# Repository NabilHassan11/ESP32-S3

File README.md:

# ESP32-S3-Mini-1-N8 Development Board

## Overview

This is a custom ESP32-S3-Mini-1-N8 development board designed for embedded systems and IoT applications. It provides an easy-to-use platform for programming, debugging, and prototyping ESP32-based projects.

## Features

✅ **RGB LED & Temperature Sensor**: Onboard RGB LED and temperature sensor for enhanced functionality

✅ **Microcontroller: ESP32-S3-Mini-1-N8 (Wi-Fi and Bluetooth LE support)**

✅ **Power Input: 3.3V regulated supply**
✅ **Reset & Boot Buttons:** Tactile push buttons for RESET and BOOT mode selection
✅ **Connectivity:** I2C header for external sensors and peripherals
    Multiple GPIO breakout pins for external components
✅ **Power Regulation:** Onboard LDO voltage regulator for stable 3.3V operation

## Applications

-IoT prototyping

-Wireless sensor networks

-Home automation

-Embedded systems development

Repository Contents

## Repository Contents
📁 **Hardware:** KiCad design files, schematics, and PCB layout
📁 **Documentation:** BOM, assembly guide, and pinout diagrams 

---
### Author
**Nabil Hassan**

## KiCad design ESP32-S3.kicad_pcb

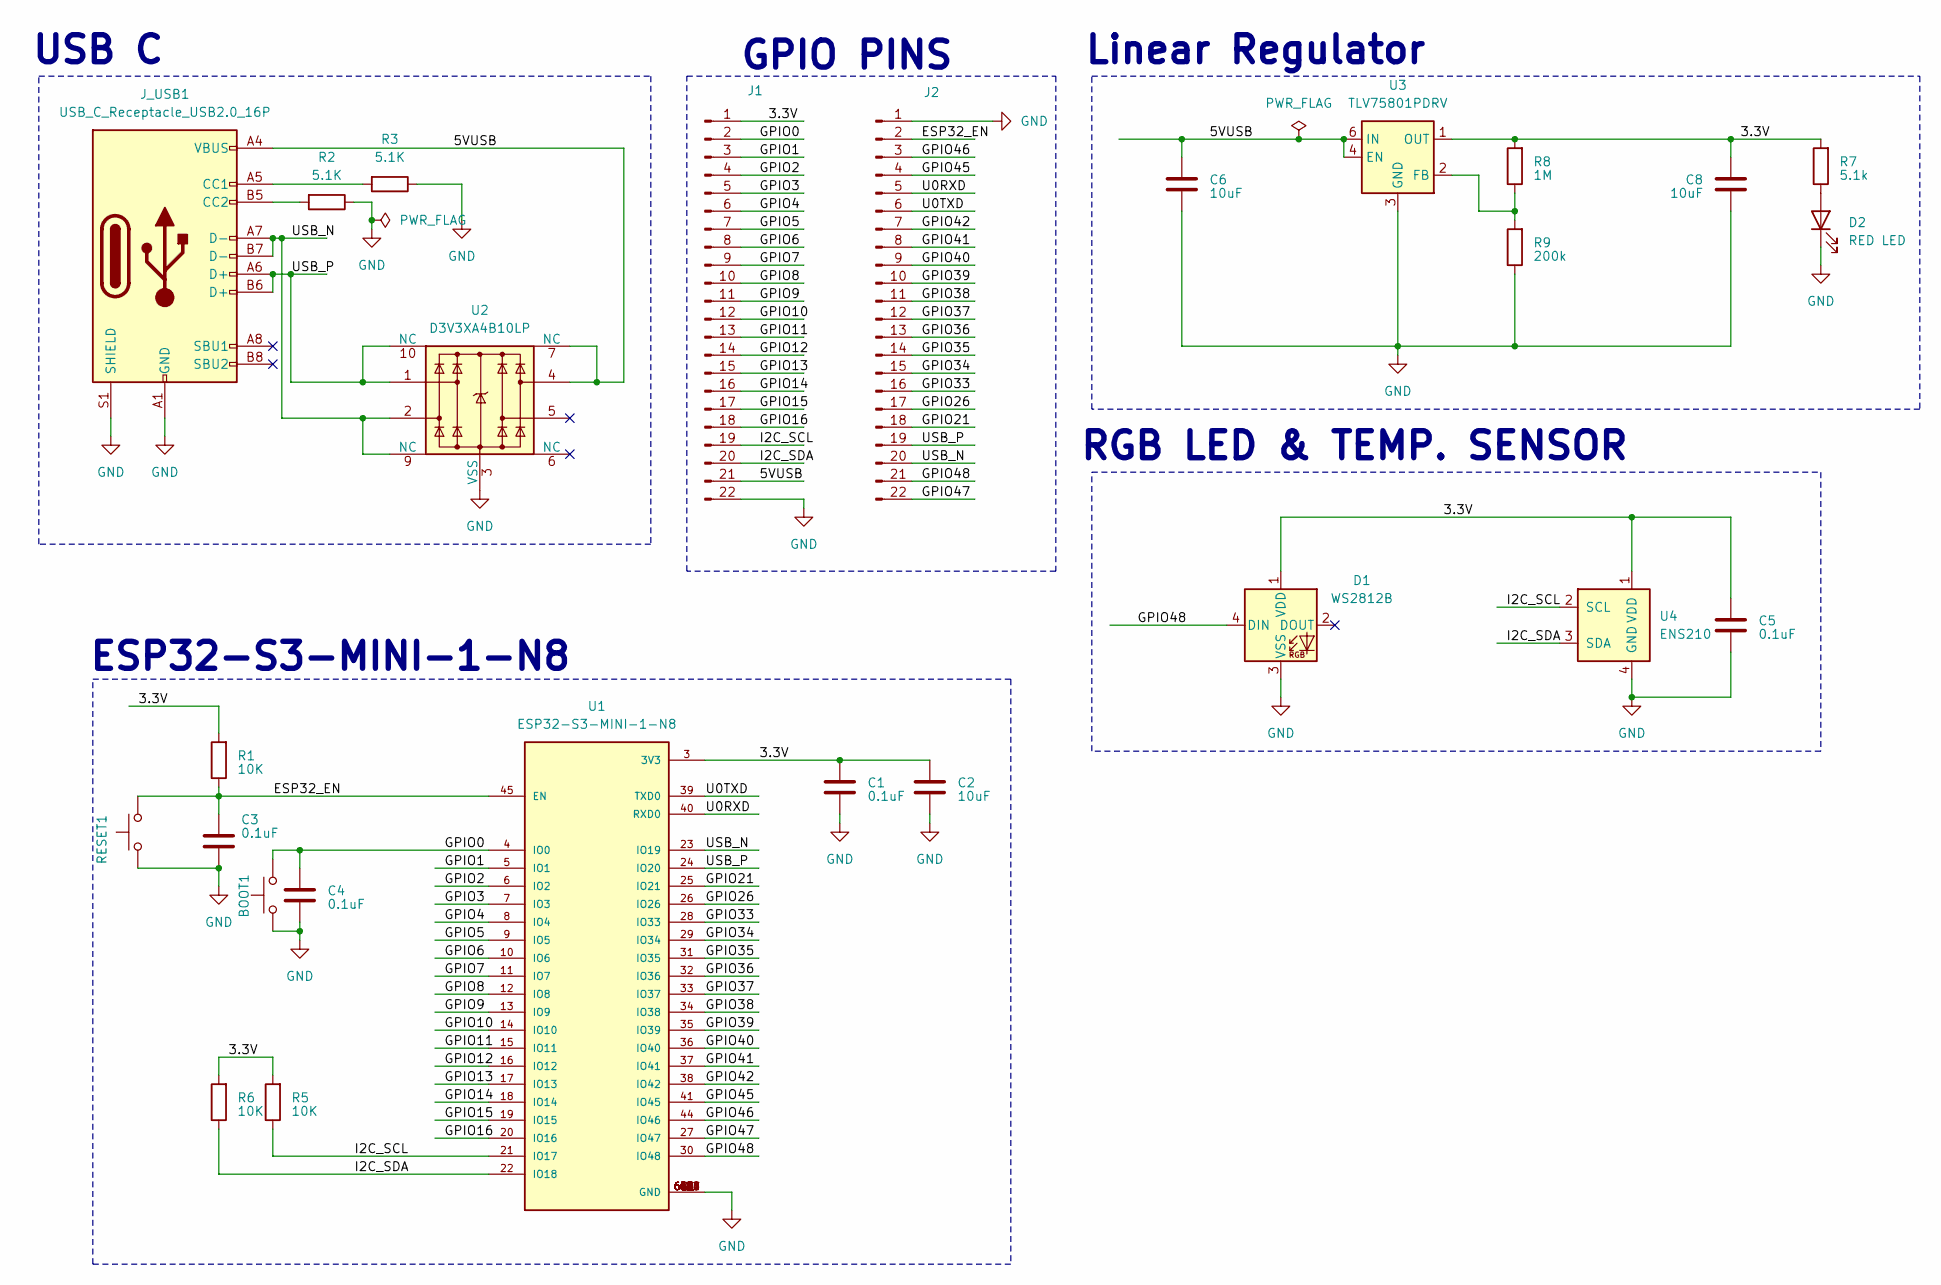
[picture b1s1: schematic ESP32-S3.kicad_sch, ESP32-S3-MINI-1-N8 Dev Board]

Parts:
BOOT1: SW_SPST_PTS810
C1, C3, C4, C5: 0.1uF; C_0201_0603Metric
C2, C6, C8: 10uF; C_0603_1608Metric
D1: WS2812B; LED_WS2812B_PLCC4_5.0x5.0mm_P3.2mm
D2: RED LED; LED_0201_0603Metric
J1, J2: Conn_01x22_Pin; PinHeader_1x22_P2.54mm_Vertical
J_USB1: USB_C_Receptacle_USB2.0_16P; USB_C_Receptacle_GCT_USB4105-xx-A_16P_TopMnt_Horizontal
R1, R5, R6: 10K; R_0201_0603Metric
R2, R3: 5.1K; R_0201_0603Metric
R7: 5.1k; R_0201_0603Metric
R8: 1M; R_0201_0603Metric
R9: 200k; R_0201_0603Metric
RESET1: SW_Push; SW_SPST_PTS810
U1: ESP32-S3-MINI-1-N8; XCVR_ESP32-S3-MINI-1-N8; PARTREV v0.6; DigiKey_Part_Number 1965-ESP32-S3-MINI-1-N8TR-ND
U2: D3V3XA4B10LP; Diodes_UDFN-10_1.0x2.5mm_P0.5mm
U3: TLV75801PDRV; WSON-6-1EP_2x2mm_P0.65mm_EP1x1.6mm
U4: ENS210; AMS_QFN-4-1EP_2x2mm_P0.95mm_EP0.7x1.6mm

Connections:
/3.3V: C1.1, C2.1, C5.1, C8.1, D1.1 (VDD), J1.1, R1.2, R5.2, R6.2, R7.2, R8.2, U1.3 (3V3), U3.1 (OUT), U4.1 (VDD)
/5VUSB: C6.1, J1.21, J_USB1.A4 (VBUS), J_USB1.A9 (VBUS), J_USB1.B4 (VBUS), J_USB1.B9 (VBUS), U2.4, U2.7 (NC), U3.4 (EN), U3.6 (IN)
/ESP32_EN: C3.1, J2.2, R1.1, RESET1.2, U1.45 (EN)
/GPIO0: BOOT1.2, C4.1, J1.2, U1.4 (IO0)
/GPIO1: J1.3, U1.5 (IO1)
/GPIO2: J1.4, U1.6 (IO2)
/GPIO3: J1.5, U1.7 (IO3)
/GPIO4: J1.6, U1.8 (IO4)
/GPIO5: J1.7, U1.9 (IO5)
/GPIO6: J1.8, U1.10 (IO6)
/GPIO7: J1.9, U1.11 (IO7)
/GPIO8: J1.10, U1.12 (IO8)
/GPIO9: J1.11, U1.13 (IO9)
/GPIO10: J1.12, U1.14 (IO10)
/GPIO11: J1.13, U1.15 (IO11)
/GPIO12: J1.14, U1.16 (IO12)
/GPIO13: J1.15, U1.17 (IO13)
/GPIO14: J1.16, U1.18 (IO14)
/GPIO15: J1.17, U1.19 (IO15)
/GPIO16: J1.18, U1.20 (IO16)
/GPIO21: J2.18, U1.25 (IO21)
/GPIO26: J2.17, U1.26 (IO26)
/GPIO33: J2.16, U1.28 (IO33)
/GPIO34: J2.15, U1.29 (IO34)
/GPIO35: J2.14, U1.31 (IO35)
/GPIO36: J2.13, U1.32 (IO36)
/GPIO37: J2.12, U1.33 (IO37)
/GPIO38: J2.11, U1.34 (IO38)
/GPIO39: J2.10, U1.35 (IO39)
/GPIO40: J2.9, U1.36 (IO40)
/GPIO41: J2.8, U1.37 (IO41)
/GPIO42: J2.7, U1.38 (IO42)
/GPIO45: J2.4, U1.41 (IO45)
/GPIO46: J2.3, U1.44 (IO46)
/GPIO47: J2.22, U1.27 (IO47)
/GPIO48: D1.4 (DIN), J2.21, U1.30 (IO48)
/I2C_SCL: J1.19, R5.1, U1.21 (IO17), U4.2 (SCL)
/I2C_SDA: J1.20, R6.1, U1.22 (IO18), U4.3 (SDA)
/U0RXD: J2.5, U1.40 (RXD0)
/U0TXD: J2.6, U1.39 (TXD0)
/USB_N: J2.20, J_USB1.A7 (D-), J_USB1.B7 (D-), U1.23 (IO19), U2.2, U2.9 (NC)
/USB_P: J2.19, J_USB1.A6 (D+), J_USB1.B6 (D+), U1.24 (IO20), U2.1, U2.10 (NC)
GND: BOOT1.1, C1.2, C2.2, C3.2, C4.2, C5.2, C6.2, C8.2, D1.3 (VSS), D2.1 (K), J1.22, J2.1, J_USB1.A1 (GND), J_USB1.A12 (GND), J_USB1.B1 (GND), J_USB1.B12 (GND), J_USB1.S1 (SHIELD), R2.1, R3.1, R9.1, RESET1.1, U1.1 (GND), U1.2 (GND), U1.42 (GND), U1.43 (GND), U1.46 (GND), U1.47 (GND), U1.48 (GND), U1.49 (GND), U1.50 (GND), U1.51 (GND), U1.52 (GND), U1.53 (GND), U1.54 (GND), U1.55 (GND), U1.56 (GND), U1.57 (GND), U1.58 (GND), U1.59 (GND), U1.60 (GND), U1.61 (GND), U1.61_1 (GND), U1.61_2 (GND), U1.61_3 (GND), U1.61_4 (GND), U1.61_5 (GND), U1.61_6 (GND), U1.61_7 (GND), U1.61_8 (GND), U1.62 (GND), U1.63 (GND), U1.64 (GND), U1.65 (GND), U2.3 (VSS), U2.8 (VSS), U3.3 (GND), U3.7 (GND), U4.4 (GND), U4.5 (GND)
unnamed: D2.2 (A), R7.1
unnamed: J_USB1.A5 (CC1), R3.2
unnamed: J_USB1.B5 (CC2), R2.2
unnamed: R8.1, R9.2, U3.2 (FB)

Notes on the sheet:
USB C
GPIO PINS
Linear Regulator
RGB LED & TEMP. SENSOR
ESP32-S3-MINI-1-N8

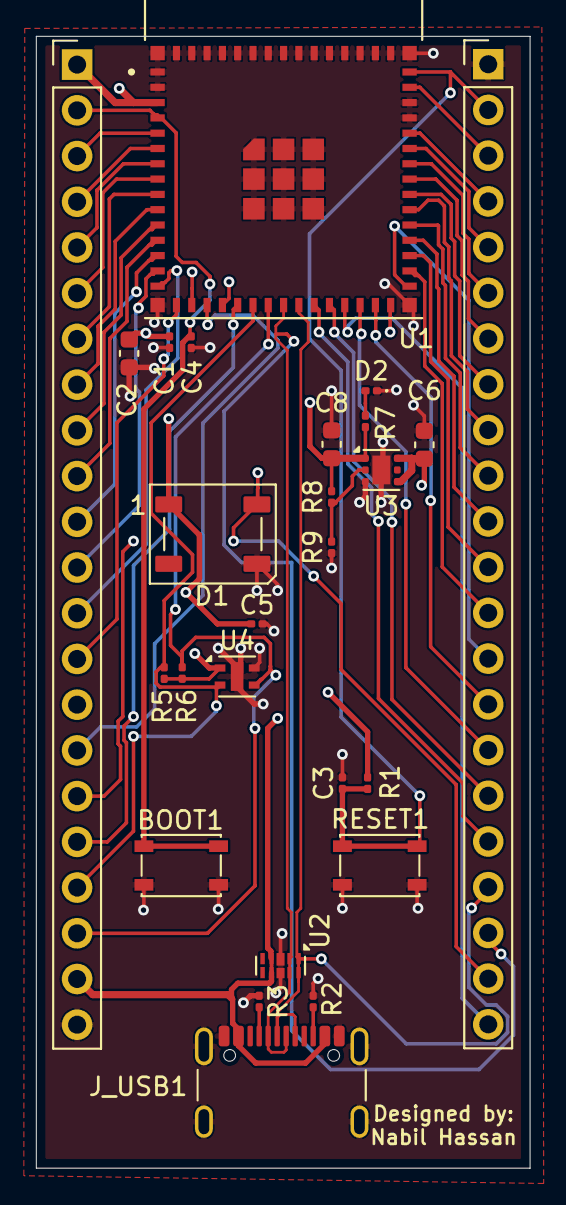
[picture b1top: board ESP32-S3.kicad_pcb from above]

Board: 4 copper layers, 27.4 x 62.9 mm, 26 parts (0 on the bottom side), 47 nets.

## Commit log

2025-05-01 Create LICENSE
